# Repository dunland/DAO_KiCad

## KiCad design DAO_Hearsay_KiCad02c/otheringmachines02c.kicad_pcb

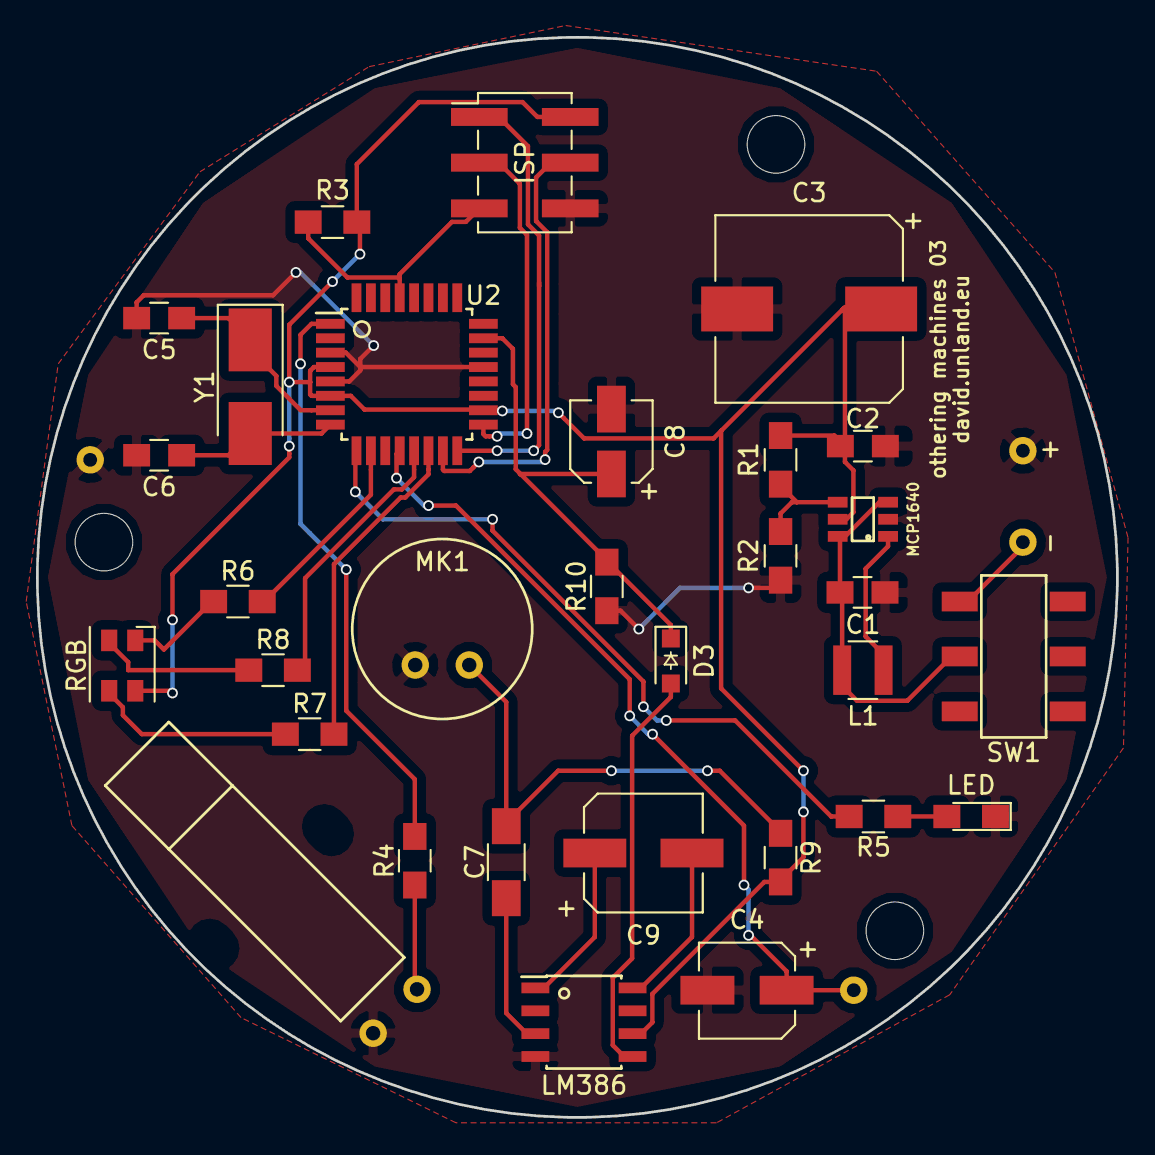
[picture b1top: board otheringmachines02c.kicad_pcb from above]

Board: 2 copper layers, 60.0 x 60.0 mm, 33 parts (0 on the bottom side), 29 nets.

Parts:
BT1: Battery; BatteryConnector
C1: 4.7uF; C_0805_HandSoldering
C2: 10uF; C_0805_HandSoldering
C3: 1000uF; CP_Elec_10x10.5
C4: 4.7uF; CP_Elec_5x5.3
C5, C6: 22pF; C_0805_HandSoldering
C7: 0.1uF; C_1206_HandSoldering
C8: 1uF; CP_Elec_4x5.3
C9: 22uF; CP_Elec_6.3x5.8
D1: LED; LED_0805_HandSoldering
D3: D; D_SOD-323_HandSoldering
ISP1: AVR-ISP-6; Pin_Header_Straight_2x03_Pitch2.54mm_SMD
L1: L; L_Abracon_ASPI-3012S
LS1: Speaker; SpeakerDigisoundSAL5050MC
M1: VibrationMotor; VibrationMotor17x5WithDrillHoles
MK1: Microphone; Microphone_Electret_WM52
R1: 68K; R_0805_HandSoldering
R2: 22K; R_0805_HandSoldering
R3: 10K; R_0805_HandSoldering
R4: 22; R_0805_HandSoldering
R5: 220; R_0805_HandSoldering
R6, R7: 1175; R_0805_HandSoldering
R8: 1600; R_0805_HandSoldering
R9: 30K; R_0805_HandSoldering
R10: 2.2K; R_0805_HandSoldering
RGB: LED_RAGB; LED_RCGB_AAA3528
SW1: SW_DIP_x01; switch_SMDslide_JS202011SCQN
U1: MCP1640; MCP1640TIchy
U2: ATMEGA328P-AU; TQFP-32_7x7mm_Pitch0.8mm
U3: LM386; SOIC-8_3.9x4.9mm_Pitch1.27mm
Y1: 16MHz; Crystal_SMD_5032-2pin_5.0x3.2mm_HandSoldering

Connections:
+2V5: BT1.1, SW1.1
/5V: C2.1, C3.1, ISP1.2, R1.1, R3.1, R9.2, RGB.2, U1.5, U2.4, U2.6, U2.18, U3.6
GND: BT1.2, C1.2, C2.2, C3.2, C4.2, C5.2, C6.2, C8.2, D1.1, ISP1.6, LS1.2, M1.2, MK1.2, R2.2, R10.1, U1.2, U2.3, U2.5, U2.21, U3.4
unnamed: C1.1, L1.2, SW1.2, U1.3, U1.6
unnamed: C4.1, LS1.1, U2.12
unnamed: C5.1, U2.7, Y1.1
unnamed: C6.1, U2.8, Y1.2
unnamed: C7.1, U3.3
unnamed: C7.2, MK1.1, R9.1
unnamed: C8.1, D3.1, R10.2, U2.23
unnamed: C9.1, U3.1
unnamed: C9.2, U3.8
unnamed: D1.2, R5.1
unnamed: R6.1, RGB.1
unnamed: R7.1, RGB.3
unnamed: R8.1, RGB.4
unnamed: D3.2, U3.5
unnamed: ISP1.1, U2.16
unnamed: ISP1.3, U2.17
unnamed: ISP1.4, U2.15
unnamed: ISP1.5, R3.2, U2.29
unnamed: L1.1, U1.1
unnamed: M1.1, R4.1
unnamed: R1.2, R2.1, U1.4
unnamed: R4.2, U2.1
unnamed: R5.2, U2.9
unnamed: R6.2, U2.10
unnamed: R7.2, U2.14
unnamed: R8.2, U2.13

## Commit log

2018-09-13 first push
    folders added
2018-09-13 drill files for laser
